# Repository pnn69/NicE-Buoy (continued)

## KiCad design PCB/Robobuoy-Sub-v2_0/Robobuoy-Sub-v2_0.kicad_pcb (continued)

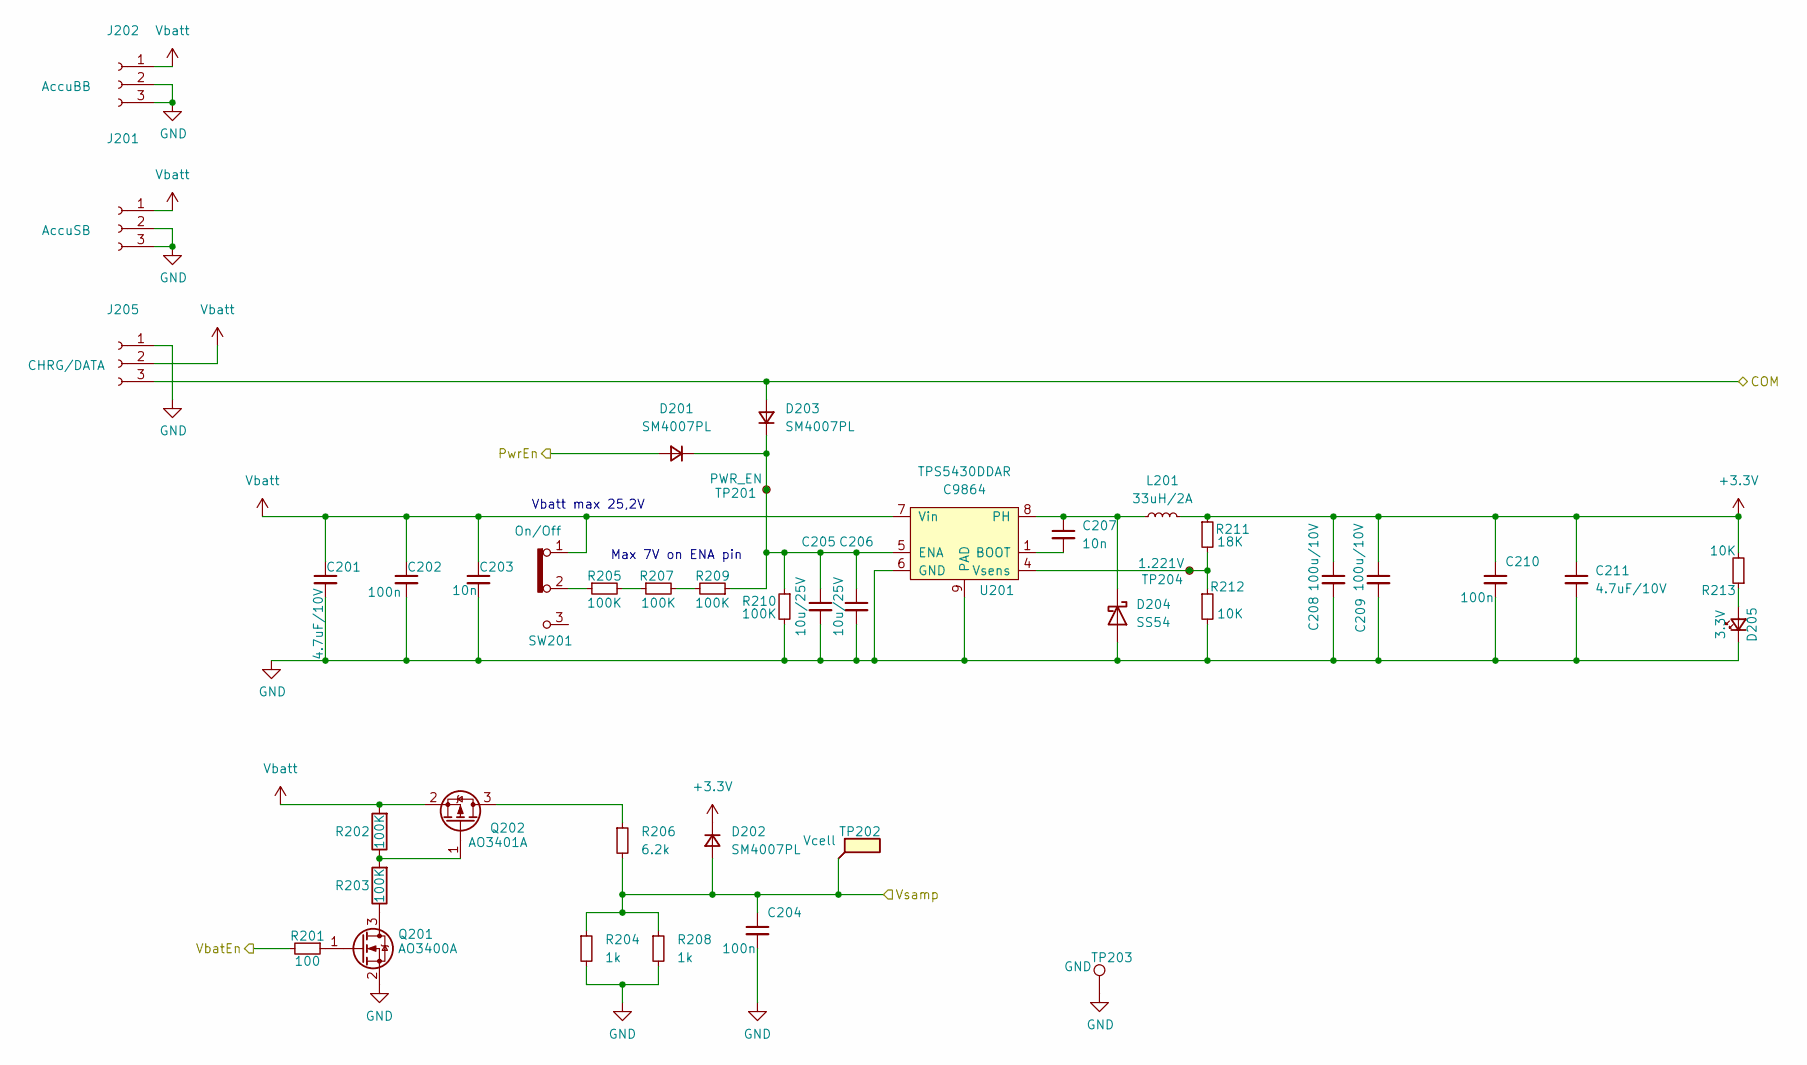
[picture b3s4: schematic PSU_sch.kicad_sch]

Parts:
C201, C211: 4.7uF/10V; C_1206_(1.6); LCSC C29823
C202, C204, C210: 100n; C_0603; LCSC C14663
C203, C207: 10n; C_0603; LCSC C57112
C205, C206: 10u/25V; C_0805; LCSC C15850
C208, C209: 100u/10V; C_1210_3225Metric; LCSC C23742
D201, D202, D203: SM4007PL; D_SOD-123_2.85x1.8x1.3; LCSC C64898
D204: SS54; D_SMA; LCSC C22452
D205: 3.3V; LED_0805; LCSC C2297
J201: AccuSB; SolderWire-0.75sqmm_1x03_P4.8mm_D1.25mm_OD2.3mm
J202: AccuBB; SolderWire-0.75sqmm_1x03_P4.8mm_D1.25mm_OD2.3mm
J205: CHRG/DATA; SolderWire-0.75sqmm_1x03_P4.8mm_D1.25mm_OD2.3mm
L201: 33uH/2A; L_6.6x7.0mm; LCSC C177245
Q201: AO3400A; SOT-23; LCSC C20917
Q202: AO3401A; SOT-23; LCSC C15127
R201: 100; R_0603; LCSC C22775
R202, R203: 100K; R_0603; Farnell 2331736
R204, R208: 1k; R_0603; LCSC C21190
R205, R207, R209, R210: 100K; R_0603; LCSC C25804
R206: 6.2k; R_0603; LCSC C25804
R211: 18K; R_0603; LCSC C25810
R212, R213: 10K; R_0603; LCSC C25804
SW201: On/Off; SS-12D10L5; LCSC C319012
TP201: PWR_EN; Testpad_1
TP202: Vcell; Testpad_1
TP203: GND; TestPoint_Loop_D2.54mm_Drill1.5mm_Beaded
TP204: 1.221V; Testpad_1
U201: TPS5430DDAR; HTSOP-8-1EP_3.9x4.9mm_P1.27mm_EP2.4x3.2mm_ThermalVias; LCSC C9864

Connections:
+3.3V: C208.1, C209.1, C210.1, C211.1, D202.1 (K), L201.2, R211.1, R213.2; also elsewhere on the board
/CPU/COM: D203.2 (A), J205.3; also elsewhere on the board
/CPU/PwrEn: D201.2 (A); also elsewhere on the board
/CPU/VbatEn: R201.2; also elsewhere on the board
/CPU/Vsamp: C204.1, D202.2 (A), R204.1, R206.2, R208.1, TP202.1; also elsewhere on the board
GND: C201.2, C202.2, C203.2, C204.2, C205.2, C206.2, C208.2, C209.2, C210.2, C211.2, D204.2 (A), D205.1 (K), J201.2, J201.3, J202.2, J202.3, J205.1, Q201.2 (S), R204.2, R208.2, R210.2, R212.2, TP203.1, U201.6 (GND), U201.9 (PAD); also elsewhere on the board
unnamed: C205.1, C206.1, D201.1 (K), D203.1 (K), R209.1, R210.1, TP201.1, U201.5 (ENA)
unnamed: C207.1, D204.1 (K), L201.1, U201.8 (PH)
unnamed: D205.2 (A), R213.1
unnamed: Q201.3 (D), R203.1
unnamed: Q201.1 (G), R201.1
unnamed: Q202.3 (D), R206.1
unnamed: Q202.1 (G), R202.1, R203.2
unnamed: R205.1, SW201.2
unnamed: R205.2, R207.1
unnamed: R207.2, R209.2
unnamed: C207.2, U201.1 (BOOT)
unnamed: R211.2, R212.1, TP204.1, U201.4 (Vsens)
Vbatt: C201.1, C202.1, C203.1, J201.1, J202.1, J205.2, Q202.2 (S), R202.2, SW201.1, U201.7 (Vin); also elsewhere on the board

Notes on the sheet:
Vbatt max 25,2V
Max 7V on ENA pin

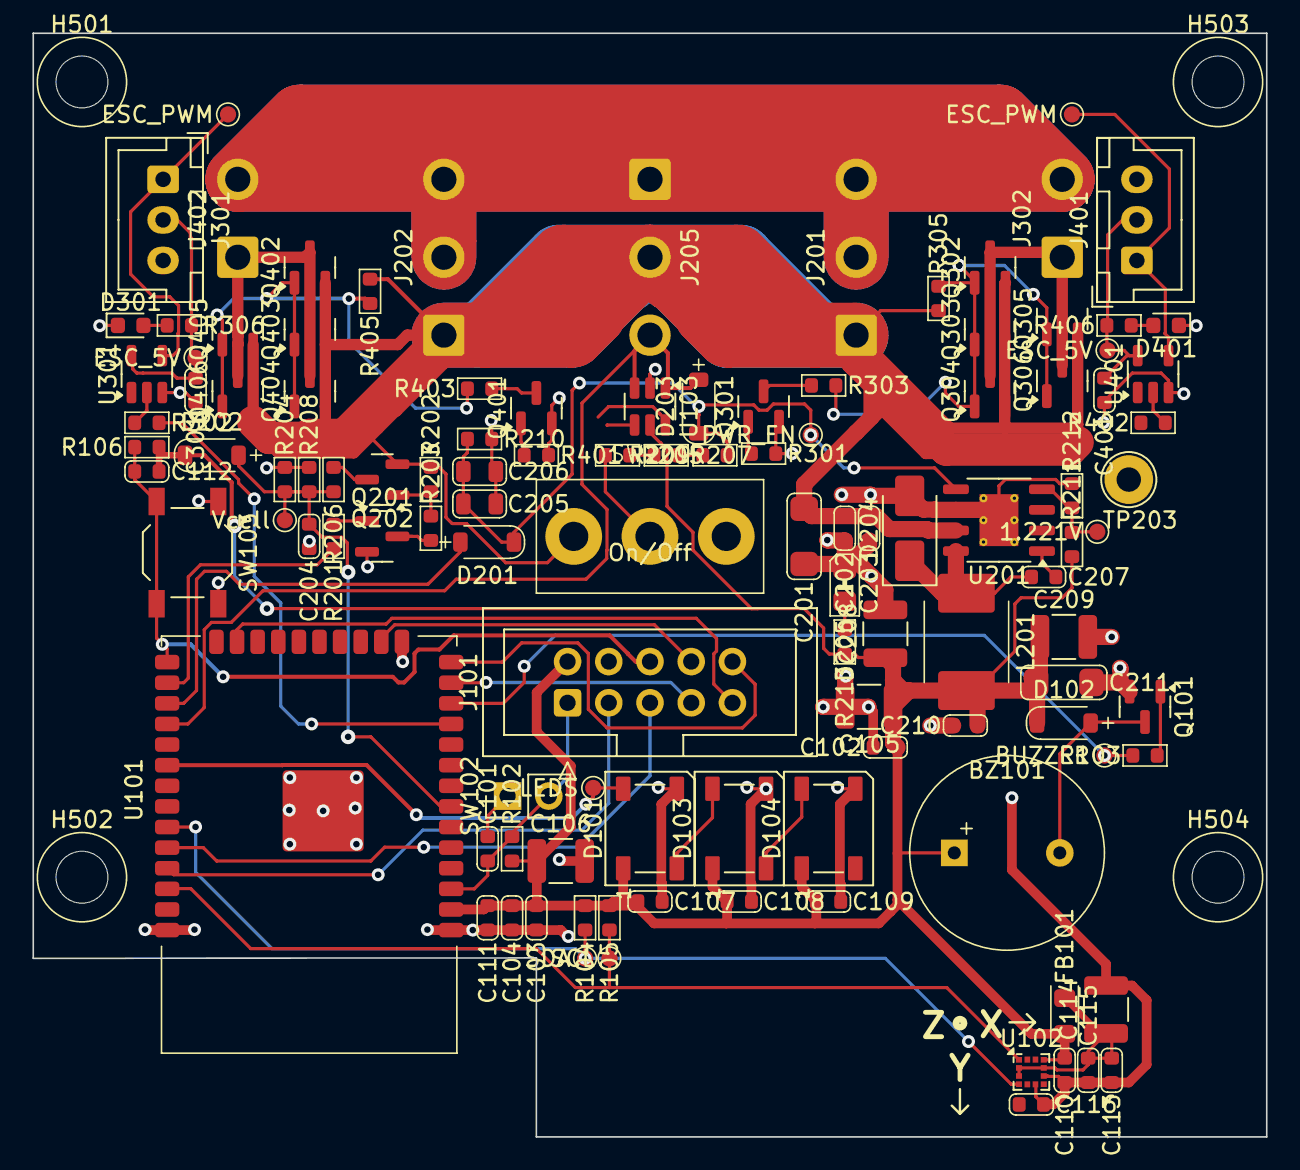
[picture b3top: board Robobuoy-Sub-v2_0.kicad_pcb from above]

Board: 4 copper layers, 76.0 x 68.0 mm, 119 parts (0 on the bottom side), 55 nets.

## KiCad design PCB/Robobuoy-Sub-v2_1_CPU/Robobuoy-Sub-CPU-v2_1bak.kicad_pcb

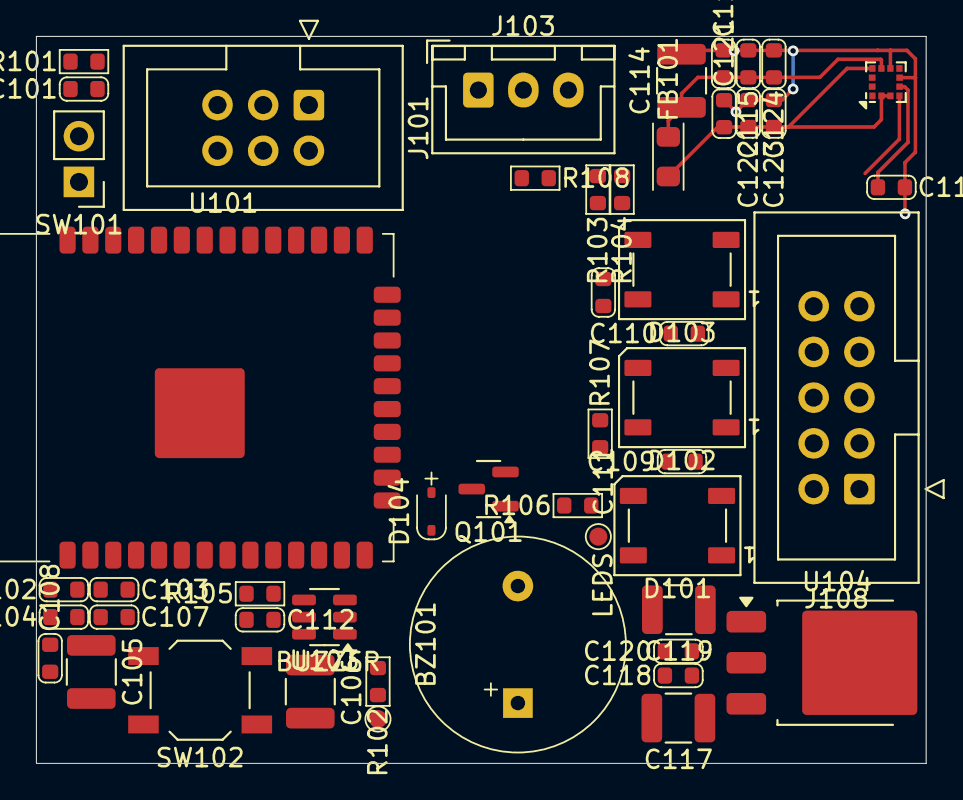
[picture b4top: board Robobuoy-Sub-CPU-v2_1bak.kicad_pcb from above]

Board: 2 copper layers, 49.4 x 40.4 mm, 50 parts (0 on the bottom side), 28 nets.

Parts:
BZ101: Buzzer; Buzzer-12x6.5x5.2
C101, C102, C103, C104, C107, C108, C109, C110, C111, C113, C116, C118, C120, C121: 100n; C_0603
C105, C106, C114, C117, C119: 100u/10V; C_1210_3225Metric
C112, C115, C122: 10n; C_0603
C123, C124: 1n; C_0603
D101, D102, D103: WS2812B; LED_WS2812B_PLCC4_5.0x5.0mm_P3.2mm
D104: 1N4148WS; D_SOD-323_1.8x1.4x1.15
FB101: 0.3E 240E@100MHz; L_0805_(1.2)
J101: Prog; IDC-Header_2x03_P2.54mm_Vertical
J103: ESC_BB; JST_XH_B3B-XH-A_1x03_P2.50mm_Vertical
J108: TO PSU; IDC-Header_2x05_P2.54mm_Vertical
Q101: AO3400A; SOT-23
R101, R105, R107: 10K; R_0603
R102, R106, R108: 100; R_0603
R103, R104: 2.2k; R_0603
SW101: ~{RESET}; PinHeader_1x02_P2.54mm_Vertical
SW102: MODE; SW_SPST_TL3342
TP101: LEDS; Testpad_1
TP102: BUZZER; Testpad_1
U101: ESP32-WROOM-32E_(visible_peripherals); ESP32-WROOM-32
U102: LSM303AGRTR; LGA-12_2x2mm_P0.5mm
U103: USBLC6-4SC6; SOT-23-6
U104: LM1117DT-3.3; TO-252-3_TabPin2

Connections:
+3.3V: C102.1, C103.1, C104.1, C105.1, C106.1, C107.1, C108.1, C112.2, C119.1, C120.1, C121.1, C122.2, C123.2, FB101.1, J101.2, R101.1, R103.1, R104.1, R105.1, R107.1, U101.2 (VDD), U102.2 (CS_XL), U102.3 (CS_MAG), U102.10 (VDDIO), U103.5 (VBUS), U104.2 (VO)
+5V: BZ101.1 (+), C109.1, C110.1, C111.1, C117.1, C118.1, D101.1 (VDD), D102.1 (VDD), D103.1 (VDD), D104.1 (K), J103.1, J108.2, U104.3 (VI)
BUZZER: R102.2, TP102.1, U101.8 (GPIO32)
COMM: J108.6, R107.2, U101.12 (GPIO27), U103.6 (I/O4)
DR0: J101.6, U101.25 (BOOT/GPIO0)
EN: C101.1, J101.1, R101.2, SW101.2, U101.3 (CHIP_PU/EN)
ESC_BB: J108.3, U101.11 (GPIO26), U103.4 (I/O3)
ESC_BB_PWR: J108.5, U101.16 (MTCK/MOSI/D3/GPIO13)
ESC_SB: J108.7, U101.13 (MTMS/SCK/CLK/GPIO14), U103.3 (I/O2)
ESC_SB_PWR: J108.9, U101.10 (GPIO25)
GND: C101.2, C102.2, C103.2, C104.2, C105.2, C106.2, C107.2, C108.2, C109.2, C110.2, C111.2, C113.2, C114.2, C115.1, C116.2, C117.2, C118.2, C119.2, C120.2, C121.2, C122.1, C123.1, C124.1, D101.3 (VSS), D102.3 (VSS), D103.3 (VSS), J101.4, J103.3, J108.1, J108.10, Q101.2 (S), SW101.1, SW102.1, U101.1 (GND), U101.15 (GND), U101.38 (GND), U101.39 (GND), U102.6 (GND), U102.8 (GND), U103.2 (GND), U104.1 (GND)
LEDS: R106.2, U101.26 (D1/GPIO4)
unnamed: BZ101.2 (-), D104.2 (A), Q101.3 (D)
unnamed: D101.4 (DIN), R106.1, TP101.1
unnamed: D101.2 (DOUT), D102.4 (DIN)
unnamed: D102.2 (DOUT), D103.4 (DIN)
unnamed: D103.2 (DOUT), R108.2
unnamed: J103.2, R108.1
unnamed: Q101.1 (G), R102.1
unnamed: R104.2, U101.36 (SCL/GPIO22), U102.1 (SCL/SPC)
unnamed: R103.2, U101.33 (SDA/GPIO21), U102.4 (SDA/SDI/SDO)
unnamed: C116.1, U102.5 (C1)
unnamed: C113.1, C114.1, C115.2, C124.2, FB101.2, U102.9 (VDD)
ON: J108.8, U101.14 (MTDI/MISO/D2/GPIO12), U103.1 (I/O1)
RX: J101.5, U101.34 (RXD/GPIO3)
SWITCH: C112.1, R105.2, SW102.2, U101.9 (GPIO33)
TX: J101.3, U101.35 (TXD/GPIO1)
VSAMP: J108.4, U101.7 (GPIO35)

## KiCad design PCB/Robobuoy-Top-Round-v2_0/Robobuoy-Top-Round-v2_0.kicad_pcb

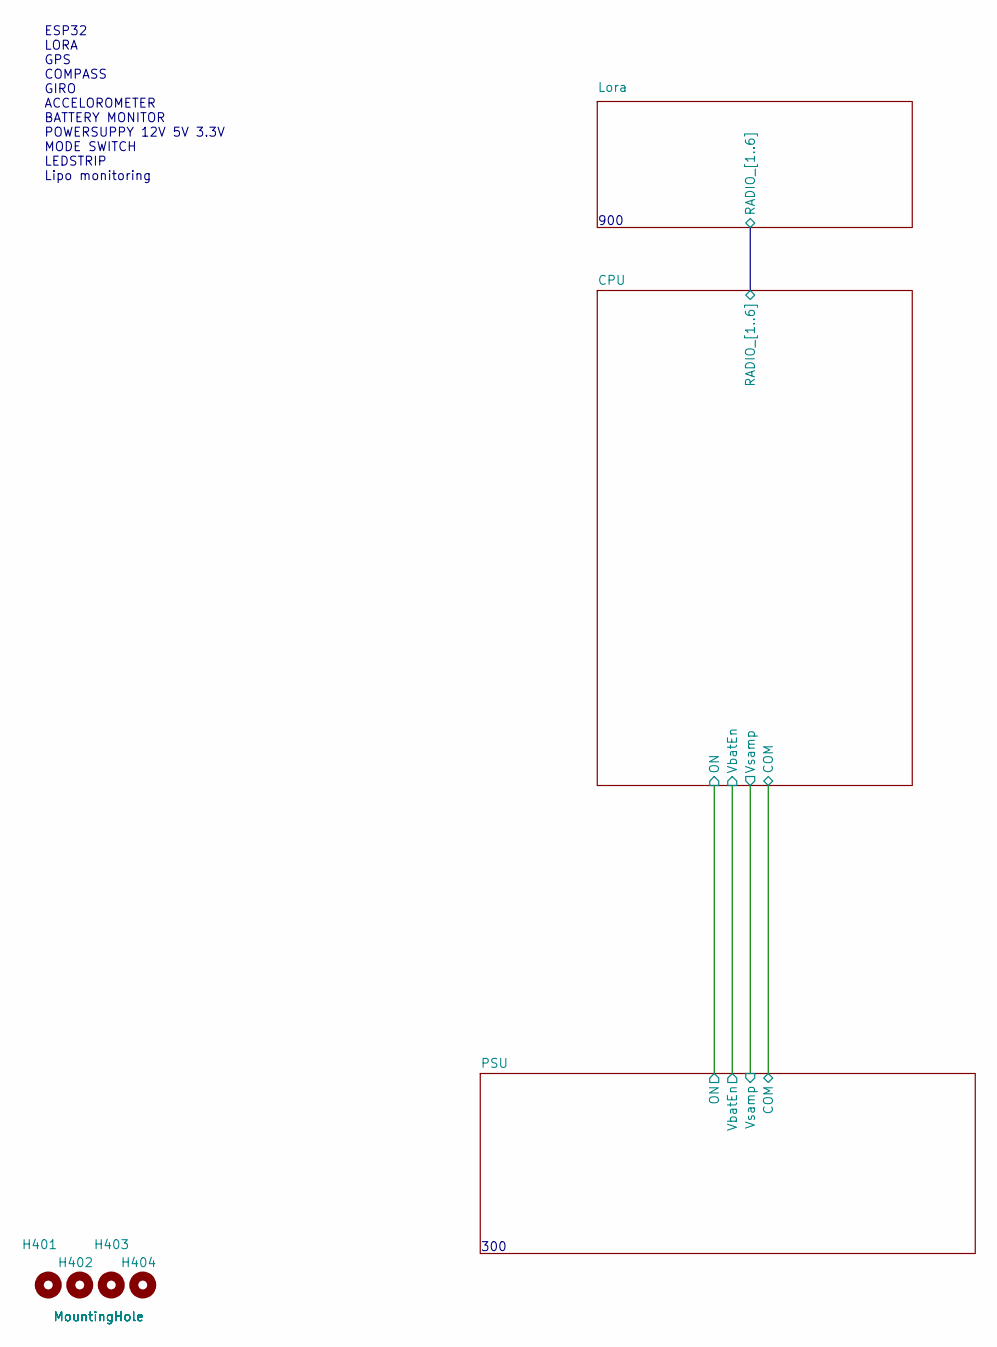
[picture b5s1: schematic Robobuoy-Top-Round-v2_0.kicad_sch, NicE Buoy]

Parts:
H401, H402, H403, H404: MountingHole; NPTH_M3

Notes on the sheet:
300
ESP32 LORA GPS COMPASS GIRO ACCELOROMETER BATTERY MONITOR POWERSUPPY 12V 5V 3.3V MODE SWITCH LEDSTRIP Lipo monitoring
900

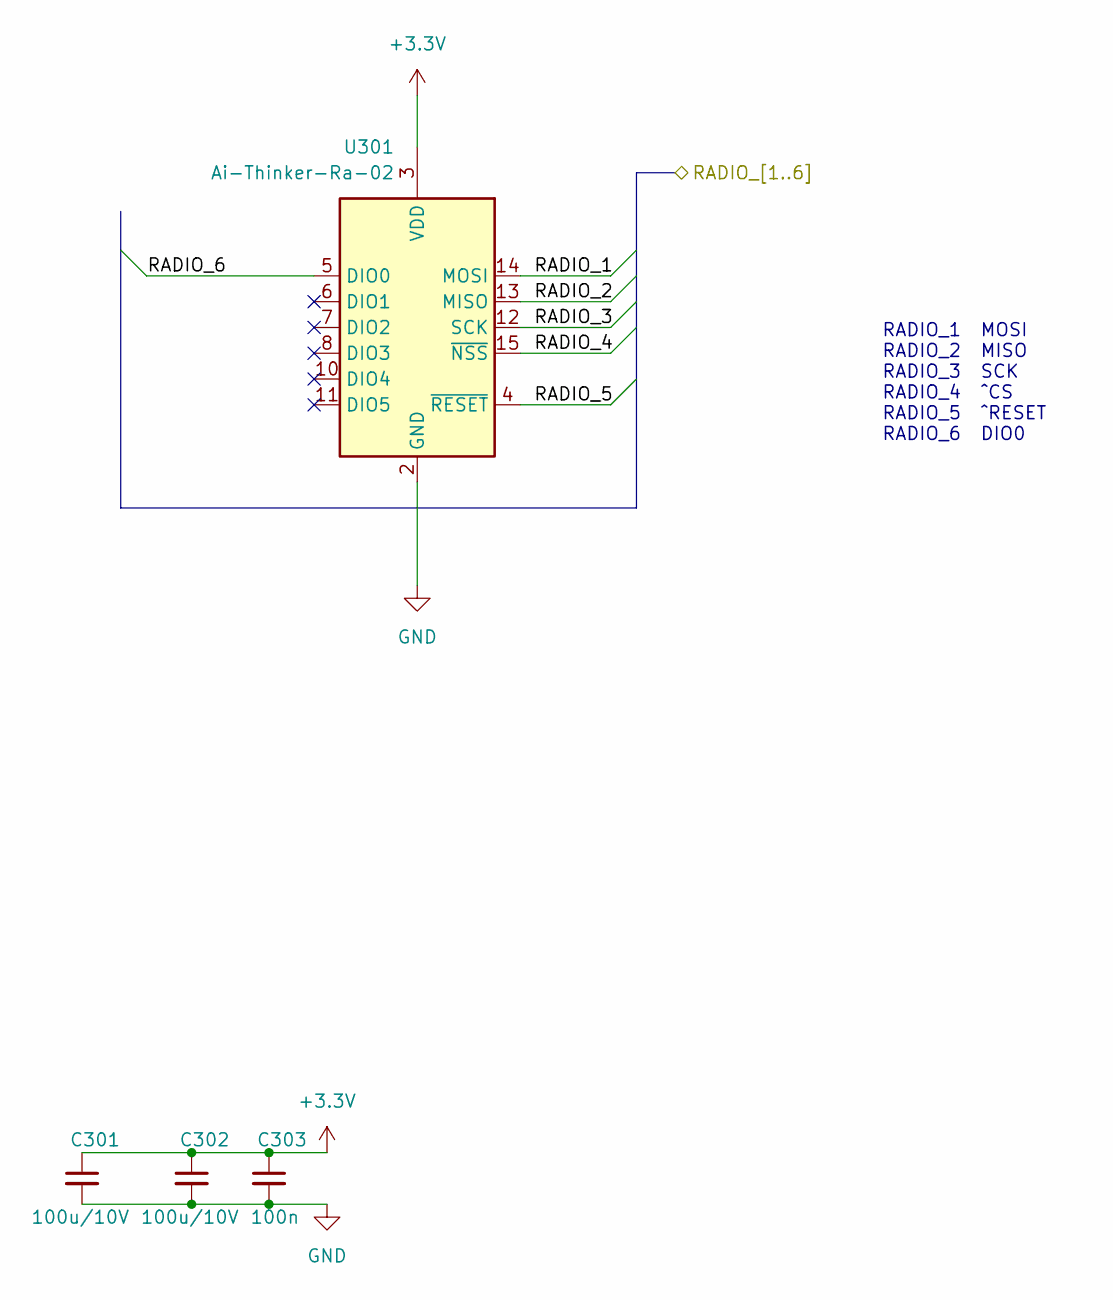
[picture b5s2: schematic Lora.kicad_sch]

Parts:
C301, C302: 100u/10V; C_1210_3225Metric; LCSC C23742
C303: 100n; C_0603; LCSC C14663
U301: Ai-Thinker-Ra-02; Ai-Thinker-Ra-02-LoRa; LCSC C90039

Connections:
+3.3V: C301.1, C302.1, C303.1, U301.3 (VDD); also elsewhere on the board
/CPU/RADIO_1: U301.14 (MOSI); also elsewhere on the board
/CPU/RADIO_2: U301.13 (MISO); also elsewhere on the board
/CPU/RADIO_3: U301.12 (SCK); also elsewhere on the board
/CPU/RADIO_4: U301.15 (~NSS); also elsewhere on the board
/CPU/RADIO_5: U301.4 (~RESET); also elsewhere on the board
/CPU/RADIO_6: U301.5 (DIO0); also elsewhere on the board
GND: C301.2, C302.2, C303.2, U301.1 (GND), U301.2 (GND), U301.9 (GND), U301.16 (GND); also elsewhere on the board

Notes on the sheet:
RADIO_1 MOSI RADIO_2 MISO RADIO_3 SCK RADIO_4 ^CS RADIO_5 ^RESET RADIO_6 DIO0

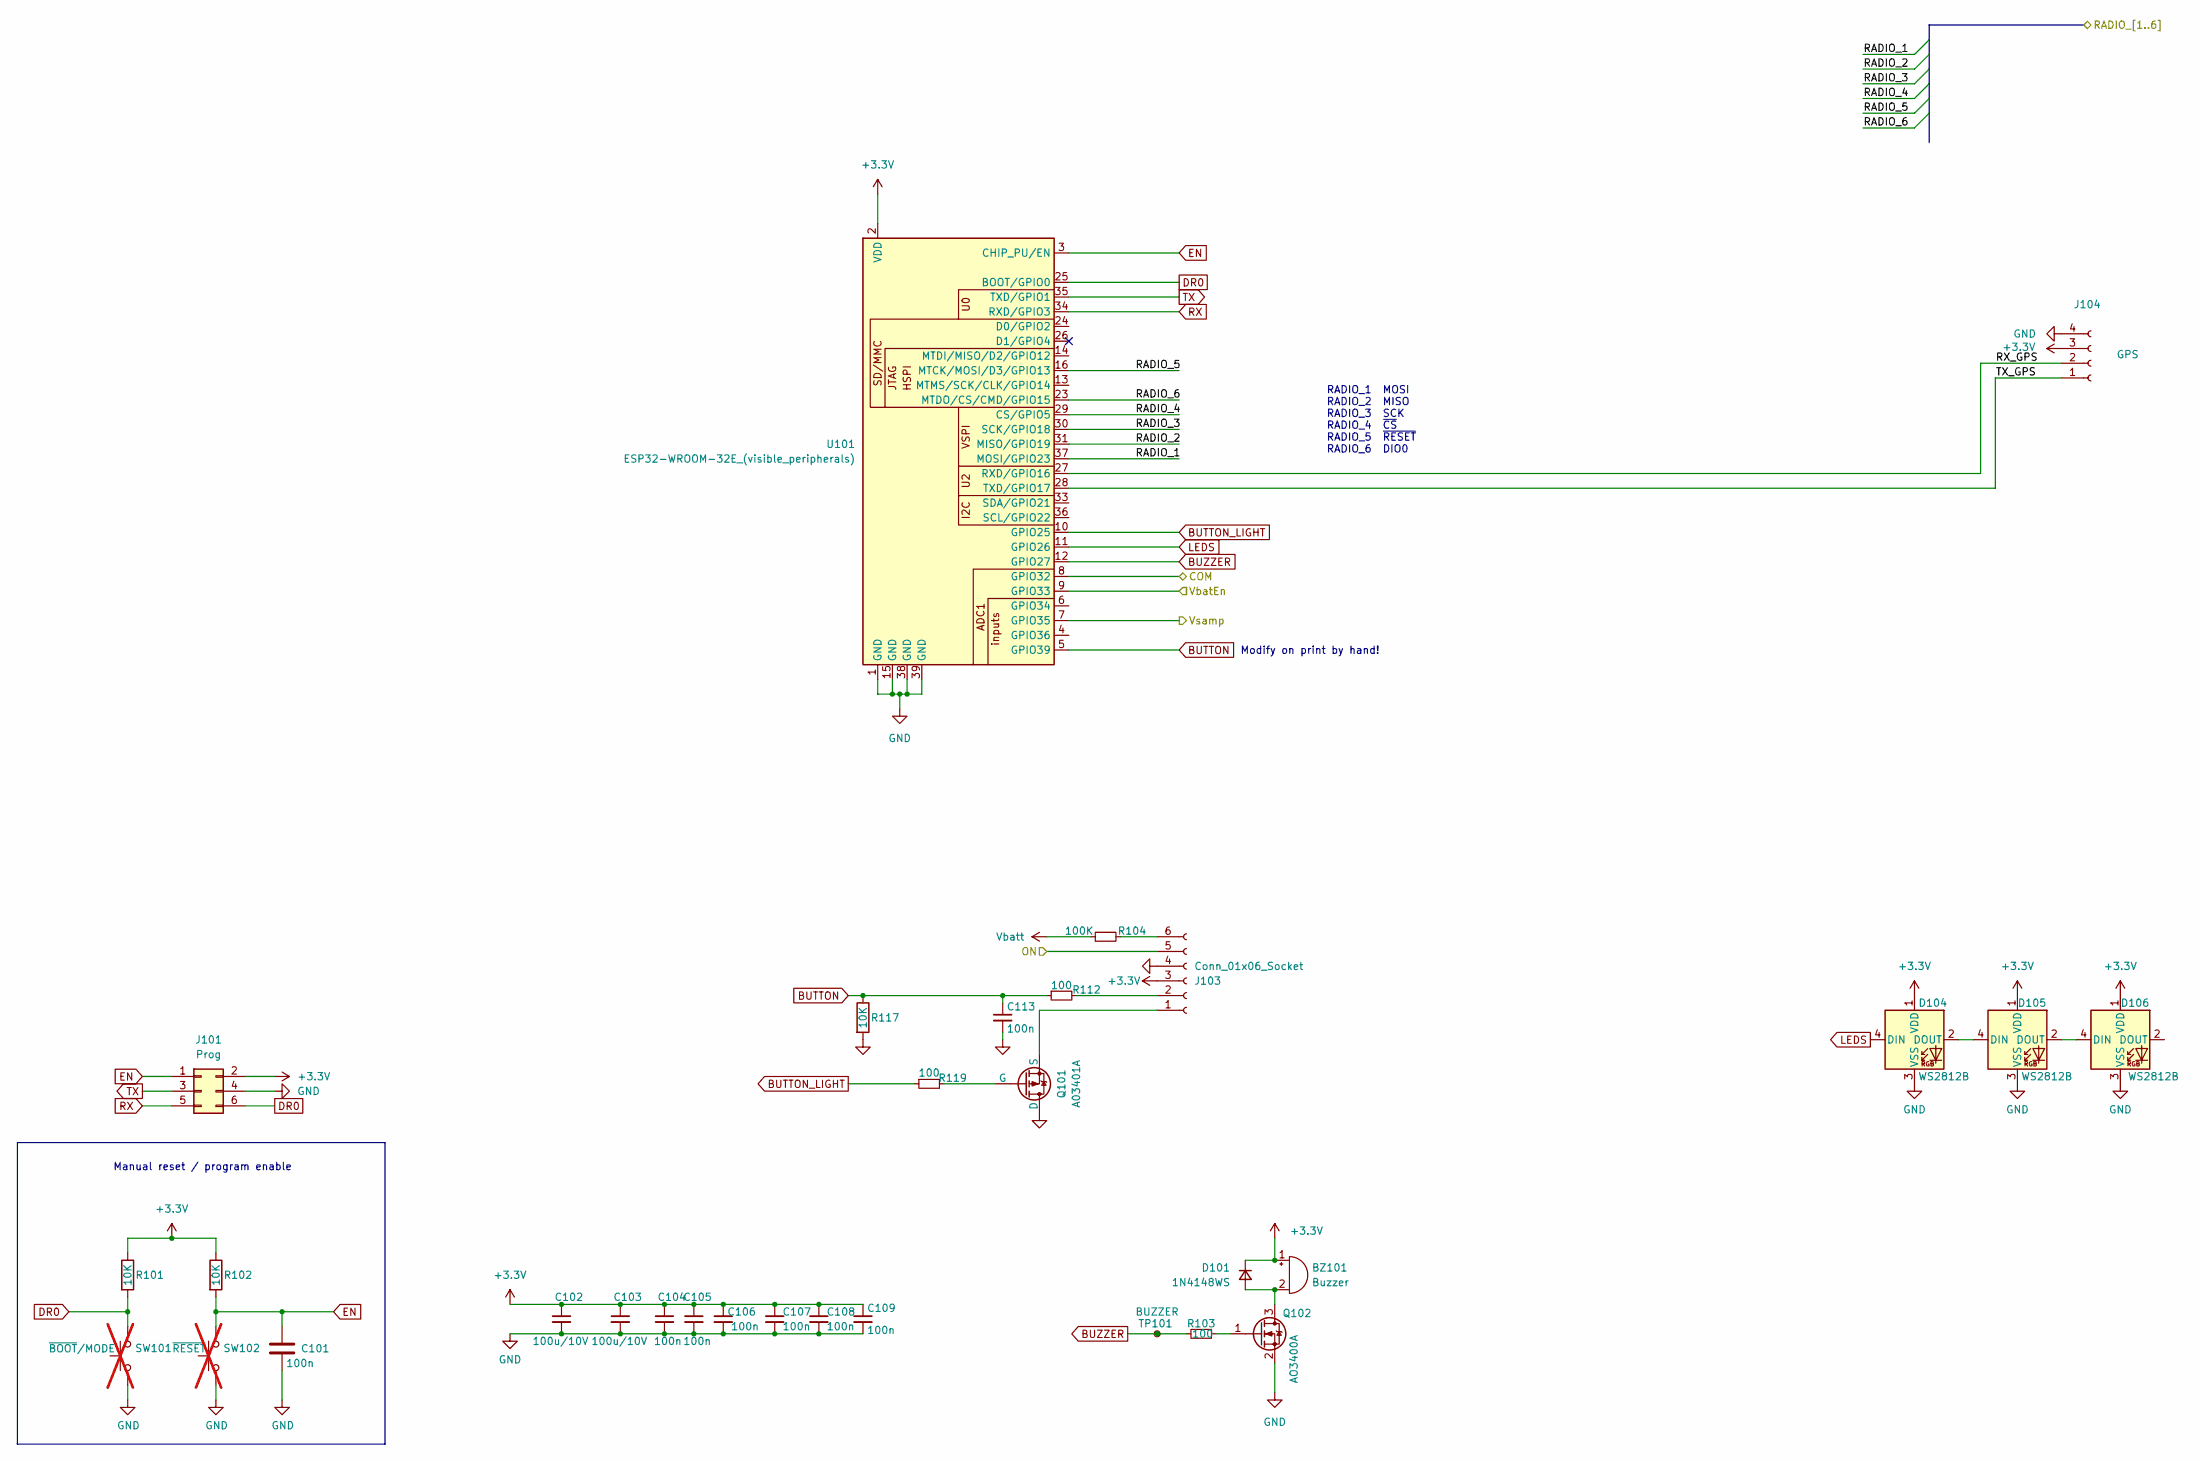
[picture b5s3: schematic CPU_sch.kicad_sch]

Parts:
BZ101: Buzzer; Buzzer-12x6.5x5.2; LCSC C968749
C101, C104, C105, C106, C107, C108, C109, C113: 100n; C_0603; LCSC C14663
C102, C103: 100u/10V; C_1210_3225Metric; LCSC C23742
D101: 1N4148WS; D_SOD-323_1.8x1.4x1.15; LCSC C2128
D104, D105, D106: WS2812B; LED_WS2812B_PLCC4_5.0x5.0mm_P3.2mm; LCSC C2843785
J101: Prog; IDC-Header_2x03_P2.54mm_Vertical; LCSC C65114
J103: Conn_01x06_Socket; JST_XH_B6B-XH-A_1x06_P2.50mm_Vertical; LCSC C5341205
J104: GPS; JST_XH_B4B-XH-A_1x04_P2.50mm_Vertical; LCSC C5341203
Q101: A03401A; SOT-23; LCSC C15127
Q102: AO3400A; SOT-23; LCSC C20917
R101, R102, R117: 10K; R_0603; Farnell 2331736
R103, R112, R119: 100; R_0603; LCSC C22775
R104: 100K; R_0603; LCSC C25804
SW101: ~{BOOT}/MODE; PinHeader_1x02_P2.54mm_Vertical; not fitted
SW102: ~{RESET}; PinHeader_1x02_P2.54mm_Vertical; not fitted
TP101: BUZZER; Testpad_1
U101: ESP32-WROOM-32E_(visible_peripherals); ESP32-WROOM-32; LCSC C82899

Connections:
+3.3V: BZ101.1 (+), C102.1, C103.1, C104.1, C105.1, C106.1, C107.1, C108.1, C109.1, D101.1 (K), D104.1 (VDD), D105.1 (VDD), D106.1 (VDD), J101.2, J103.3, J104.3, R101.1, R102.1, U101.2 (VDD); also elsewhere on the board
/CPU/COM: U101.8 (GPIO32); also elsewhere on the board
/CPU/ON: J103.5; also elsewhere on the board
/CPU/RADIO_1: U101.37 (MOSI/GPIO23); also elsewhere on the board
/CPU/RADIO_2: U101.31 (MISO/GPIO19); also elsewhere on the board
/CPU/RADIO_3: U101.30 (SCK/GPIO18); also elsewhere on the board
/CPU/RADIO_4: U101.29 (CS/GPIO5); also elsewhere on the board
/CPU/RADIO_5: U101.16 (MTCK/MOSI/D3/GPIO13); also elsewhere on the board
/CPU/RADIO_6: U101.23 (MTDO/CS/CMD/GPIO15); also elsewhere on the board
/CPU/RX_GPS: J104.2, U101.27 (RXD/GPIO16)
/CPU/TX_GPS: J104.1, U101.28 (TXD/GPIO17)
/CPU/VbatEn: U101.9 (GPIO33); also elsewhere on the board
/CPU/Vsamp: U101.7 (GPIO35); also elsewhere on the board
BUTTON: C113.1, R112.1, R117.1, U101.5 (GPIO39)
BUTTON_LIGHT: R119.1, U101.10 (GPIO25)
BUZZER: R103.2, TP101.1, U101.12 (GPIO27)
DR0: J101.6, R101.2, SW101.2, U101.25 (BOOT/GPIO0)
EN: C101.1, J101.1, R102.2, SW102.2, U101.3 (CHIP_PU/EN)
GND: C101.2, C102.2, C103.2, C104.2, C105.2, C106.2, C107.2, C108.2, C109.2, C113.2, D104.3 (VSS), D105.3 (VSS), D106.3 (VSS), J101.4, J103.4, J104.4, Q101.1 (D), Q102.2 (S), R117.2, SW101.1, SW102.1, U101.1 (GND), U101.15 (GND), U101.38 (GND), U101.39 (GND); also elsewhere on the board
LEDS: D104.4 (DIN), U101.11 (GPIO26)
unnamed: BZ101.2 (-), D101.2 (A), Q102.3 (D)
unnamed: D104.2 (DOUT), D105.4 (DIN)
unnamed: D105.2 (DOUT), D106.4 (DIN)
unnamed: J103.1, Q101.3 (S)
unnamed: J103.2, R112.2
unnamed: J103.6, R104.2
unnamed: Q101.2 (G), R119.2
unnamed: Q102.1 (G), R103.1
RX: J101.5, U101.34 (RXD/GPIO3)
TX: J101.3, U101.35 (TXD/GPIO1)
Vbatt: R104.1; also elsewhere on the board

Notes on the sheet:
Modify on print by hand!
RADIO_1 MOSI RADIO_2 MISO RADIO_3 SCK RADIO_4 ~{CS} RADIO_5 ~{RESET} RADIO_6 DIO0
Manual reset / program enable

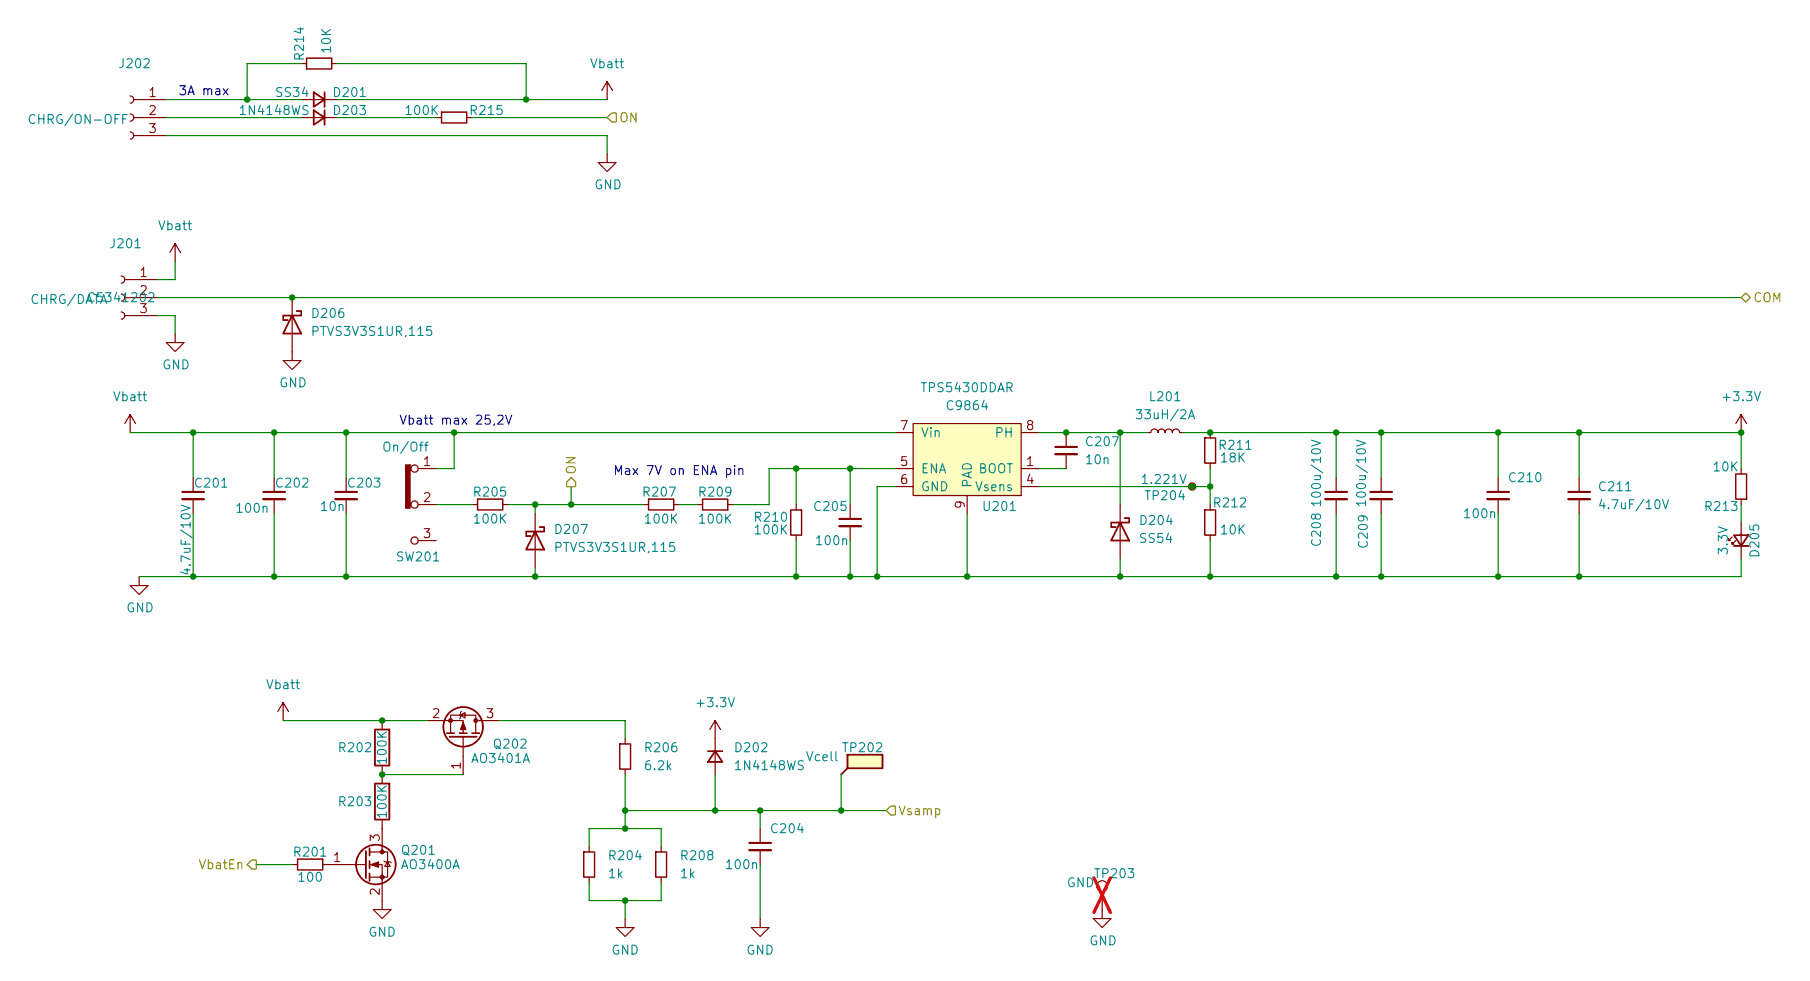
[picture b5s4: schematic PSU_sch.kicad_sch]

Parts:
C201, C211: 4.7uF/10V; C_1206_(1.6); LCSC C29823
C202, C204, C205, C210: 100n; C_0603; LCSC C14663
C203, C207: 10n; C_0603; LCSC C57112
C208, C209: 100u/10V; C_1210_3225Metric; LCSC C23742
D201: SS34; D_SMA; LCSC C8678
D202, D203: 1N4148WS; D_SOD-323_1.8x1.4x1.15; LCSC C2128
D204: SS54; D_SMA; LCSC C22452
D205: 3.3V; LED_0805; LCSC C2297
D206, D207: PTVS3V3S1UR,115; D_SOD-123; LCSC C183521
J201: CHRG/DATA; JST_XH_B3B-XH-A_1x03_P2.50mm_Vertical; LCSC C5341202
J202: CHRG/ON-OFF; JST_XH_B3B-XH-A_1x03_P2.50mm_Vertical; LCSC C5341202
L201: 33uH/2A; L_6.6x7.0mm; LCSC C177245
Q201: AO3400A; SOT-23; LCSC C20917
Q202: AO3401A; SOT-23; LCSC C15127
R201: 100; R_0603; LCSC C22775
R202, R203: 100K; R_0603; Farnell 2331736
R204, R208: 1k; R_0603; LCSC C21190
R205, R207, R209, R210, R215: 100K; R_0603; LCSC C25804
R206: 6.2k; R_0603; LCSC C25804
R211: 18K; R_0603; LCSC C25810
R212, R213, R214: 10K; R_0603; LCSC C25804
SW201: On/Off; Header_1x03_P2.54_Male; LCSC C2937625
TP202: Vcell; Testpad_1
TP203: GND; TestPoint_Loop_D2.54mm_Drill1.5mm_Beaded; not fitted
TP204: 1.221V; Testpad_1
U201: TPS5430DDAR; HTSOP-8-1EP_3.9x4.9mm_P1.27mm_EP2.4x3.2mm_ThermalVias; LCSC C9864

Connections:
+3.3V: C208.1, C209.1, C210.1, C211.1, D202.1 (K), L201.2, R211.1, R213.2; also elsewhere on the board
/CPU/COM: D206.1 (K), J201.2; also elsewhere on the board
/CPU/ON: D207.1 (K), R205.2, R207.1, R215.2; also elsewhere on the board
/CPU/VbatEn: R201.2; also elsewhere on the board
/CPU/Vsamp: C204.1, D202.2 (A), R204.1, R206.2, R208.1, TP202.1; also elsewhere on the board
GND: C201.2, C202.2, C203.2, C204.2, C205.2, C208.2, C209.2, C210.2, C211.2, D204.2 (A), D205.1 (K), D206.2 (A), D207.2 (A), J201.3, J202.3, Q201.2 (S), R204.2, R208.2, R210.2, R212.2, TP203.1, U201.6 (GND), U201.9 (PAD); also elsewhere on the board
unnamed: D201.2 (A), J202.1, R214.1
unnamed: D203.2 (A), J202.2
unnamed: D203.1 (K), R215.1
unnamed: C207.1, D204.1 (K), L201.1, U201.8 (PH)
unnamed: D205.2 (A), R213.1
unnamed: Q201.3 (D), R203.1
unnamed: Q201.1 (G), R201.1
unnamed: Q202.3 (D), R206.1
unnamed: Q202.1 (G), R202.1, R203.2
unnamed: R205.1, SW201.2
unnamed: R207.2, R209.2
unnamed: C207.2, U201.1 (BOOT)
unnamed: C205.1, R209.1, R210.1, U201.5 (ENA)
unnamed: R211.2, R212.1, TP204.1, U201.4 (Vsens)
Vbatt: C201.1, C202.1, C203.1, D201.1 (K), J201.1, Q202.2 (S), R202.2, R214.2, SW201.1, U201.7 (Vin); also elsewhere on the board

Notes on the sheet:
Max 7V on ENA pin
Vbatt max 25,2V
3A max

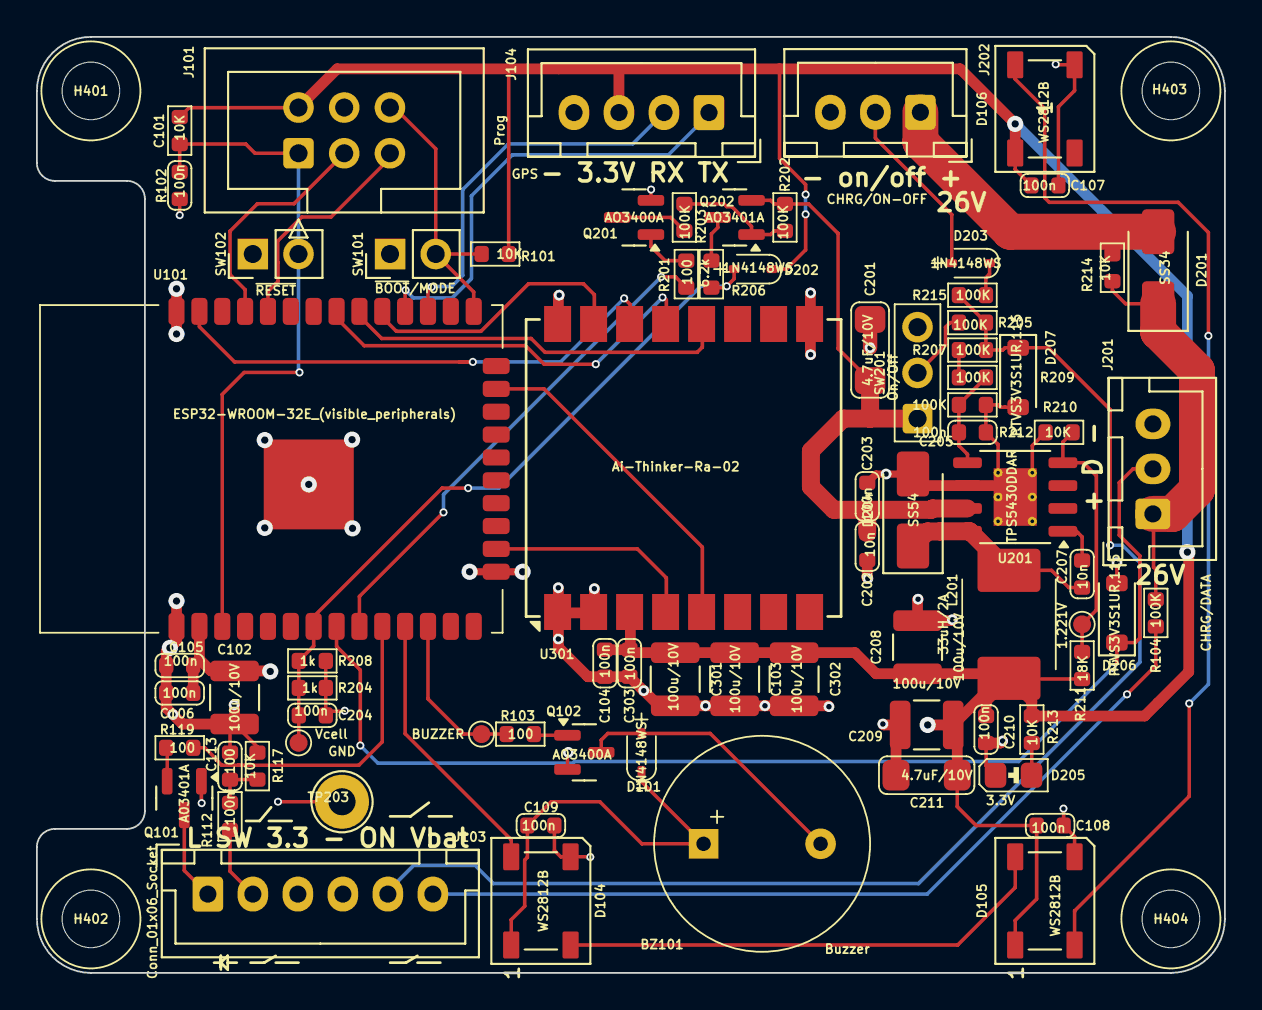
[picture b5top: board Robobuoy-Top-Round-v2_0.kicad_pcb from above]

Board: 4 copper layers, 66.0 x 52.0 mm, 81 parts (0 on the bottom side), 45 nets.
